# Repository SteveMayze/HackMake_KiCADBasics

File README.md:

# Hack & Make KiCAD Basics
The project files developed for the Hack &amp; Make Nuremberg Meeting.

## Objective
This class is aimed at those who would like to create their own PCB designs but don't know where to start. 
The idea is to make a 45 minute to an hour presentation on the basics of KiCAD. It would only briefly cover 
the installation and then dive into the creation of a layout. The purpose of this approach is to demonstrate 
the following points 

1. It is possible to only create the PCB layout - but more importantly, 
1. To demonstrate why it is important to consider the workflow for board design and using KiCAD.

The presentation should cover such things as creating a circuit, association footprints to the symbols and 
then formally creating the layout again with the support of the software.

## The Repository
This repository will contain the files developed to support the presentation. There are two models. One for 
the first part of the presentation. This is a reference model as it is envisaged to create this model from scratch
during the presentation. The second model is distributed over several directories. Each representing specific 
steps. The idea here is as follows

1. Provides neat falback points
1. Although envisaged as a presentation, there could be participants that want to follow along. This provides
the artifacts so that they can pick up at the current spot in the presentation rather than loosing the thread
of the presentation because of catching up.

The first model is a simple LED, resistor and battery circuit. As mentioned earlier, this will be created 
on the fly, from scratch. The second model will be a "Blinky" based on the 555 timer. The details of the 
circuit won't be discussed. 

## What needs to be covered

1. Project Structure - The files in the dirctory ( file extensions )
1. Menu Layout - The important points
1. Program Navigation - The various modules
1. Schematic Editor
   1. The Symbol Editor
1. The PCB Layout tool
   1. Hotkeys
   1. The footprint editor
   1. The 3D viewer
   1. The Gerber viewer

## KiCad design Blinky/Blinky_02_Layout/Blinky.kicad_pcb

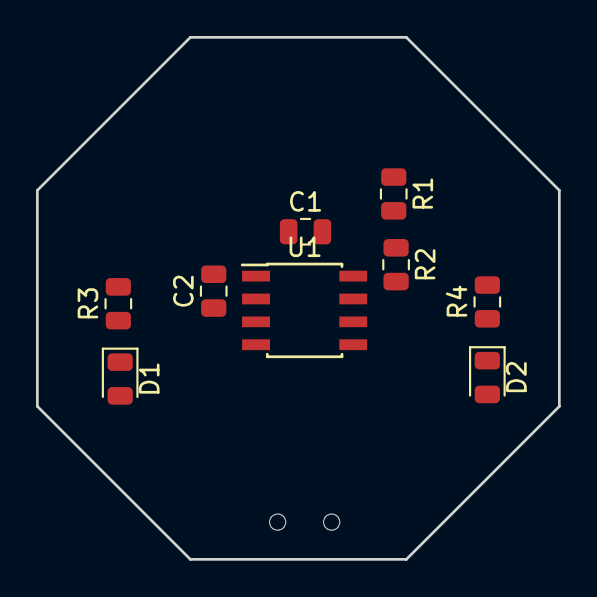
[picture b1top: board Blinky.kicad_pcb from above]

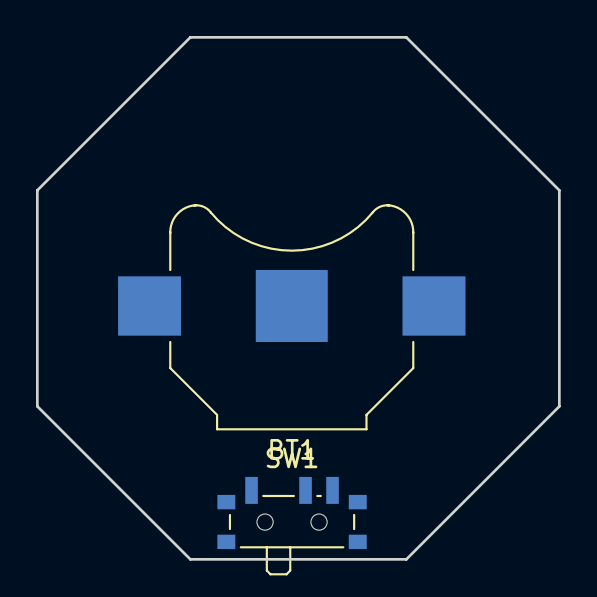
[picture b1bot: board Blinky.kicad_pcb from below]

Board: 2 copper layers, 29.0 x 29.0 mm, 11 parts (2 on the bottom side), 8 nets, no tracks yet.

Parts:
BT1: 3V Cell; BatteryHolder_Keystone_3000_1x12mm
C1: 300n; C_0805_2012Metric
C2: 0.1u; C_0805_2012Metric
D1, D2: LED; LED_0805_2012Metric
R1: 10k; R_0805_2012Metric
R2: 1M; R_0805_2012Metric
R3, R4: 200; R_0805_2012Metric
SW1: SW_SPDT; SW_SPDT_PCM12
U1: NE555; SOIC-8_3.9x4.9mm_P1.27mm

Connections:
/Vcc: C2.1, D1.2, R1.1, SW1.3, U1.4, U1.8
GND: BT1.2, C1.2, C2.2, R4.2, U1.1
unnamed: BT1.1, SW1.2
unnamed: C1.1, R2.2, U1.2, U1.6
unnamed: D1.1, R3.1
unnamed: D2.1, R4.1
unnamed: D2.2, R3.2, U1.3
unnamed: R1.2, R2.1, U1.7

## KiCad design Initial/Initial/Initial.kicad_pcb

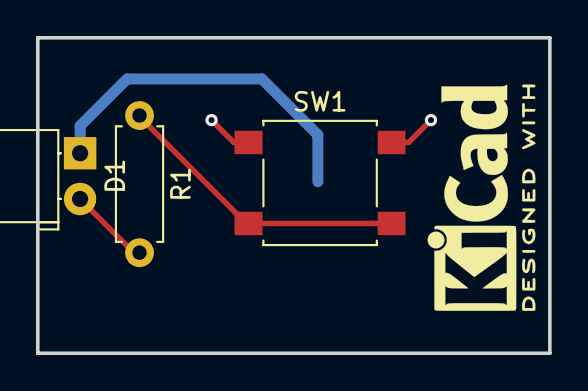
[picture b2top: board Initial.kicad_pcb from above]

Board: 2 copper layers, 28.4 x 17.5 mm, 4 parts (1 on the bottom side), 4 nets.

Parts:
BT1: 3V CR1220; BatteryHolder_Keystone_3000_1x12mm
D1: LED; LED_D5.0mm_Horizontal_O1.27mm_Z3.0mm
R1: 100Ω; R_Axial_DIN0207_L6.3mm_D2.5mm_P7.62mm_Horizontal
SW1: SW_SPST; SW_SPST_B3S-1000

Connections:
unnamed: BT1.1, SW1.1
unnamed: BT1.2, D1.1
unnamed: D1.2, R1.2
unnamed: R1.1, SW1.2

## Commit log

2018-09-22 Started the HackMake Nuremberg KiCAD Basics Repo.
2018-09-22 Initial projects structure and templates
2018-09-22 Added prints of the final schematic and layout
2018-09-22 Added the mounting hole that was removed during the cleanup
2018-09-22 Printed a new reference layout PDF
2018-09-22 Adds the PDF of the final layout for the first half of the presentation
2018-09-22 Small typo in the readme file
2018-09-22 Created a model BOM
2018-10-20 Fixed the relative path for the symbol libraries
2018-10-22 Added the datasheet
2018-10-22 Changed the gitignore for DS_Store
2018-10-22 Added the kewnotes
2018-11-01 Removed the not-connected symbol
2018-11-01 New Base model for the presentation
2018-11-01 Base line ... again
2018-11-01 Removed annotation
2018-11-01 Baseline ...
2018-11-01 Baseline.. removed the Vcc label from 01_Layout
2018-11-01 Added the default edge cut
2018-11-01 Updated the final layout PDF
2018-11-02 Corrected the Project Variable
2018-11-02 Removed a wire label
2018-11-02 Resetting Schematic 1.
2018-11-02 Removed the octagonal edge cut
2018-11-02 03 Layout partially done
2018-11-02 Added another slide, just in case
2018-11-02 Refit for Windows
